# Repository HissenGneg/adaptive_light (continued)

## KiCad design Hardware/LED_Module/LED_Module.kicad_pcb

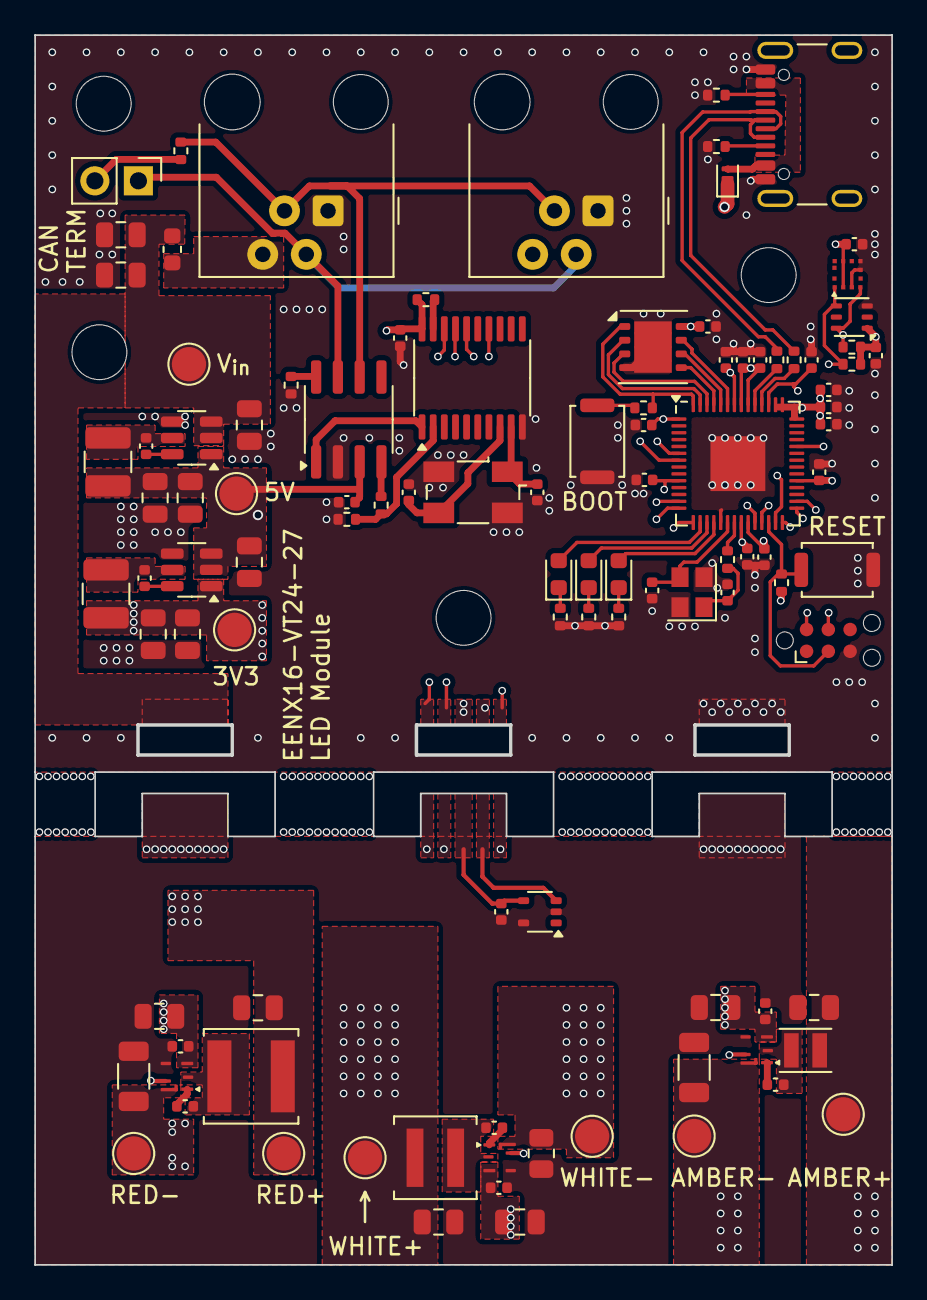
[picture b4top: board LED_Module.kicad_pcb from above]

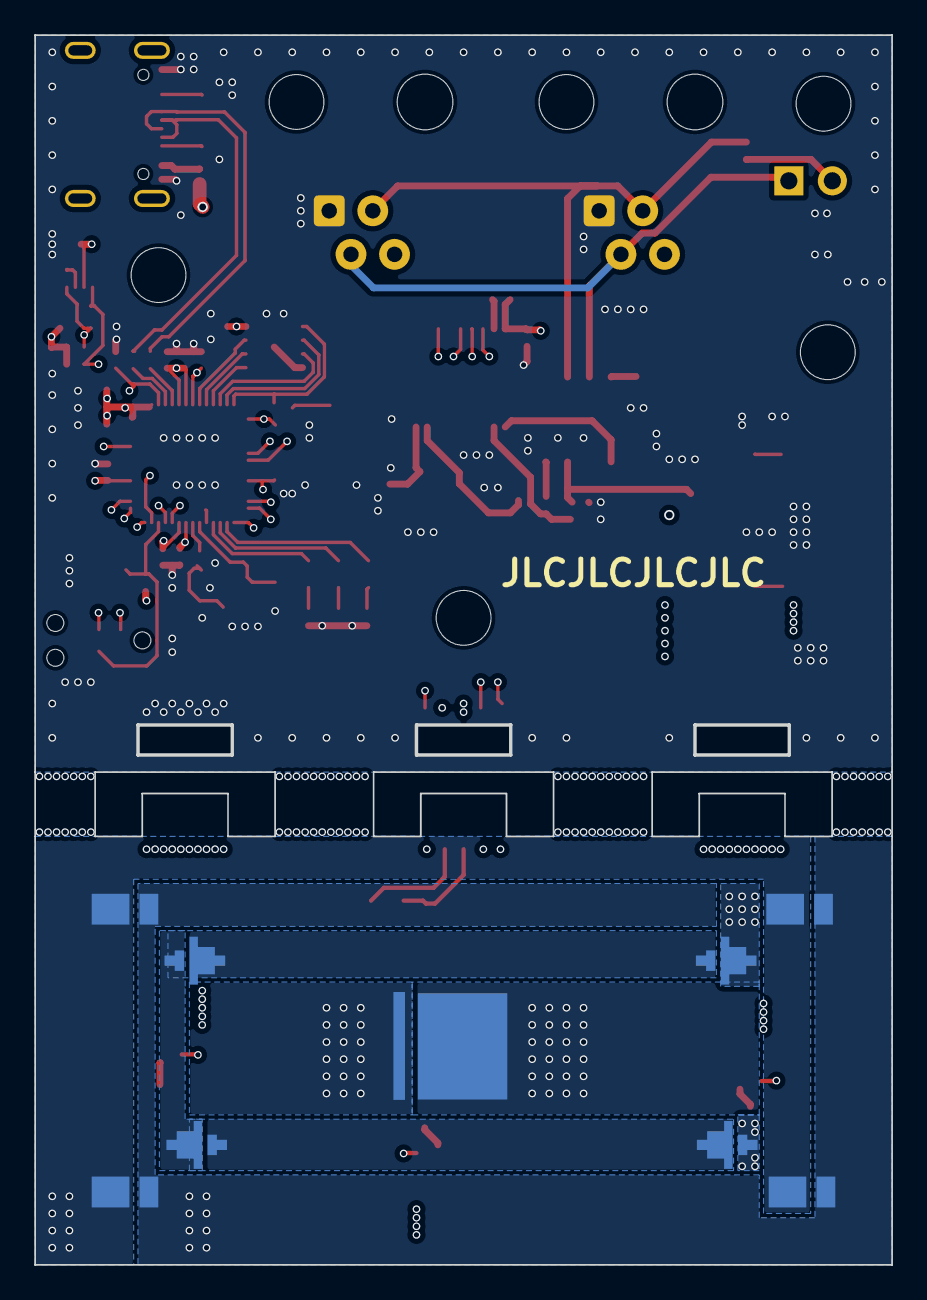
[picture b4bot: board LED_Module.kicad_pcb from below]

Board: 4 copper layers, 50.0 x 71.8 mm, 117 parts (9 on the bottom side), 71 nets.

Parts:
C201, C202, C302, C306, C501, C503, C507, C508, C509, C512: 10u; C_0805_2012Metric
C203, C204, C301, C305, C401, C402, C403, C404, C405, C406, C407, C408, C409, C411, C412, C413, C502, C504, C505, C506, C510, C511, C513, C601, C602: 100n; C_0402_1005Metric
C205, C206, C414, C415: 10p; C_0402_1005Metric
C303, C304, C307, C308: 22u; C_0805_2012Metric
C410: 1u; C_0402_1005Metric
D401: D_Schottky; Nexperia_DSN1608-2_1.6x0.8mm
D501, D503, D504, D505: LED-red; KR DMLQ32. 23
D502: LED-main; LUXEON 7070
D506, D507, D508, D509: LED-amber; JE2835_Amber
D601: R; LED_0603_1608Metric
D602: G; LED_0603_1608Metric
D603: B; LED_0603_1608Metric
F201: 4A; Fuse_0603_1608Metric
H101, H102, H103, H104: MountingHole; MountingHole_3.2mm_M3
J201, J202: RJ9; RJ9_Evercom_5301-440xxx_Horizontal
J401: USB_C_Receptacle_USB2.0_16P; USB_C_Receptacle_GCT_USB4105-xx-A_16P_TopMnt_Horizontal
J402: TagConnect_SWD; Tag-Connect_TC2030-IDC-NL_2x03_P1.27mm_Vertical
JP201: Jumper_termination; PinHeader_1x02_P2.54mm_Vertical
L301, L302: 4u7; L_1210_3225Metric
L501: 20u; L_Changjiang_FNR5045S
L502: 15u; L_Coilcraft_XAL4040-XXX
L503: 5.6u; L_Sunlord_SWPA252012S
R201, R603, R604, R605: 120; R_0402_1005Metric
R202, R401, R402, R601, R602: 5k1; R_0402_1005Metric
R203, R204, R205, R403: 10k; R_0402_1005Metric
R404, R407: 1k; R_0402_1005Metric
R405, R406: 27; R_0402_1005Metric
R501: 100m; R_0805_2012Metric
R502, R503: 200m; R_1206_3216Metric
SW401, SW402: SW_Push; SW_Push_SPST_NO_Alps_SKRK
TP201: TPVin; TestPoint_Pad_D2.0mm
TP301: TP3V3; TestPoint_Pad_D2.0mm
TP302: TP5V; TestPoint_Pad_D2.0mm
TP501: TPLED2+; TestPoint_Pad_D2.0mm
TP502: TPLED1+; TestPoint_Pad_D2.0mm
TP503: TPLED1-; TestPoint_Pad_D2.0mm
TP504: TPLED2-; TestPoint_Pad_D2.0mm
TP505: TPLED3+; TestPoint_Pad_D2.0mm
TP506: TPLED3-; TestPoint_Pad_D2.0mm
U201: MCP2551-I-SN; SOIC-8_3.9x4.9mm_P1.27mm
U202: MCP2515-xST; TSSOP-20_4.4x6.5mm_P0.65mm
U301: AP63203WU; TSOT-23-6
U302: AP63205WU; TSOT-23-6
U401: W25Q64JVXGIQ; WSON-8-1EP_4x4mm_P0.8mm_EP2.2x3mm
U402: RP2040; QFN-56-1EP_7x7mm_P0.4mm_EP3.2x3.2mm
U501, U502, U503: TPS92200; VQFN-HR-6pin-TexasInstruments
U504: TMP236; SOT-353_SC-70-5
U601: MC3479
U602: LTR-303ALS-01; Lite-On_LTR-303ALS-01
Y201: 8M; Crystal_SMD_Abracon_ABM3B-4Pin_5.0x3.2mm
Y401: 12M; Crystal_SMD_2520-4Pin_2.5x2.0mm

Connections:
+1V1: C410.1, C411.1, C412.1, U402.23 (DVDD), U402.45 (VREG_VOUT), U402.50 (DVDD)
+3V3: C203.1, C303.1, C304.1, C401.1, C402.1, C403.1, C404.1, C405.1, C406.1, C407.1, C408.1, C409.1, C413.1, C513.1, C601.1, C602.1, L301.2, R205.1, R403.1, R601.1, R602.1, TP301.1, U202.20 (VDD), U301.1 (FB), U401.8 (VCC), U402.1 (IOVDD), U402.10 (IOVDD), U402.22 (IOVDD), U402.33 (IOVDD), U402.42 (IOVDD), U402.43 (ADC_AVDD), U402.44 (VREG_IN), U402.48 (USB_VDD), U402.49 (IOVDD), U504.4 (V_{DD}), U601.2 (CSN), U601.9 (VDD), U602.1 (VDD)
+5V: C204.1, C302.1, C307.1, C308.1, D401.1 (K), L302.2, TP302.1, U201.3 (VDD), U301.2 (EN), U301.3 (IN), U302.1 (FB)
+SYSTEM: C201.1, C202.1, C306.1, C501.1, C502.1, C503.1, C504.1, C509.1, C510.1, F201.2, TP201.1, U302.2 (EN), U302.3 (IN), U501.3 (Vin), U502.3 (Vin), U503.3 (Vin)
/CAN_bus/CANH: J201.2, J202.2, JP201.1 (A), U201.7 (CANH)
/CAN_bus/CANL: J201.3, J202.3, R201.2, U201.6 (CANL)
/LED_TEMP: U402.38 (GPIO26_ADC0), U504.3 (V_{OUT})
/MISO: U202.17 (SO), U402.27 (GPIO16)
/MOSI: U202.16 (SI), U402.30 (GPIO19)
/Microcontroller/FLASH_CLK: U401.6 (CLK), U402.52 (QSPI_SCLK)
/Microcontroller/FLASH_IO0: U401.5 (DI(IO0)), U402.53 (QSPI_SD0)
/Microcontroller/FLASH_IO1: U401.2 (DO(IO1)), U402.55 (QSPI_SD1)
/Microcontroller/FLASH_IO2: U401.3 (IO2), U402.54 (QSPI_SD2)
/Microcontroller/FLASH_IO3: U401.7 (IO3), U402.51 (QSPI_SD3)
/Microcontroller/FLASH_~CS: R404.2, U401.1 (~CS), U402.56 (QSPI_SS)
/Microcontroller/RP2040_D+: R405.2, U402.47 (USB_DP)
/Microcontroller/RP2040_D-: R406.2, U402.46 (USB_DM)
/Microcontroller/SWCLK: J402.4 (SWCLK), U402.24 (SWCLK)
/Microcontroller/SWD: J402.2 (SWDIO), U402.25 (SWD)
/Microcontroller/USB_D+: J401.A6 (D+), J401.B6 (D+), R405.1
/Microcontroller/USB_D-: J401.A7 (D-), J401.B7 (D-), R406.1
/Microcontroller/XIN: C414.2, U402.20 (XIN), Y401.3
/Microcontroller/XOUT: R407.2, U402.21 (XOUT)
/Microcontroller/XOUT_R: C415.2, R407.1, Y401.1
/Microcontroller/~RESET: J402.3 (~RESET), R403.2, SW401.1, U402.26 (RUN)
/PWM_AMBER: U402.15 (GPIO12), U503.5 (DIM)
/PWM_RED: U402.14 (GPIO11), U501.5 (DIM)
/PWM_WHITE: U402.13 (GPIO10), U502.5 (DIM)
/SCK: U202.14 (SCK), U402.29 (GPIO18)
/SCL: R601.2, U402.7 (GPIO5), U601.1 (SCK_SCL), U602.4 (SCL)
/SDA: R602.2, U402.6 (GPIO4), U601.4 (DIN_SDA), U602.6 (SDA)
/STATUS1: D603.2 (A), U402.18 (GPIO15)
/STATUS2: D601.2 (A), U402.17 (GPIO14)
/STATUS3: D602.2 (A), U402.16 (GPIO13)
/~CS: U202.18 (~CS), U402.28 (GPIO17)
GND: C201.2, C202.2, C203.2, C204.2, C205.1, C206.1, C302.2, C303.2, C304.2, C306.2, C307.2, C308.2, C401.2, C402.2, C403.2, C404.2, C405.2, C406.2, C407.2, C408.2, C409.2, C410.2, C411.2, C412.2, C413.2, C414.1, C415.1, C501.2, C502.2, C503.2, C504.2, C507.2, C508.2, C509.2, C510.2, C512.2, C513.2, C601.2, C602.2, J201.1, J202.1, J401.A1 (GND), J401.A12 (GND), J401.B1 (GND), J401.B12 (GND), J402.5 (GND), R203.2, R204.2, R401.2, R402.2, R501.2, R502.2, R503.2, R603.2, R604.2, R605.2, SW401.2, SW402.1, U201.2 (VSS), U202.10 (VSS), U301.4 (GND), U302.4 (GND), U401.4 (GND), U401.9 (EP), U402.19 (TESTEN), U402.57 (GND), U501.4 (GND), U502.4 (GND), U503.4 (GND), U504.2 (GND), U504.5 (GND), U601.3 (DOUT_A6), U601.6 (GND), U601.7 (VPP), U602.3 (GND), Y201.2, Y201.4, Y401.2, Y401.4
unnamed: D401.2 (A), J401.A4 (VBUS), J401.A9 (VBUS), J401.B4 (VBUS), J401.B9 (VBUS)
unnamed: C507.1, D501.2 (A), L501.2, TP501.1
unnamed: D501.1 (K), D503.2 (A)
unnamed: C508.1, D502.2 (A), L502.2, TP502.1
unnamed: D502.1 (K), R501.1, TP503.1, U502.6 (FB)
unnamed: D503.1 (K), D504.2 (A)
unnamed: D504.1 (K), D505.2 (A)
unnamed: D505.1 (K), R502.1, TP504.1, U501.6 (FB)
unnamed: C512.1, D506.2 (A), D507.2 (A), D508.2 (A), D509.2 (A), L503.2, TP505.1
unnamed: D506.1 (K), D507.1 (K), D508.1 (K), D509.1 (K), R503.1, TP506.1, U503.6 (FB)
unnamed: D601.1 (K), R603.1
unnamed: D602.1 (K), R604.1
unnamed: D603.1 (K), R605.1
unnamed: F201.1, J201.4, J202.4
unnamed: J401.A5 (CC1), R402.1
unnamed: J401.B5 (CC2), R401.1
unnamed: JP201.2 (B), R201.1
unnamed: R404.1, SW402.2
unnamed: R202.1, U201.4 (RXD)
unnamed: R204.1, U201.8 (Rs)
unnamed: U201.1 (TXD), U202.1 (TXCAN)
unnamed: C206.2, U202.9 (OSC1), Y201.1
unnamed: C205.2, U202.8 (OSC2), Y201.3
unnamed: R202.2, R203.1, U202.2 (RXCAN)
unnamed: R205.2, U202.19 (~RESET)
unnamed: C301.2, U301.6 (BST)
unnamed: C301.1, L301.1, U301.5 (SW)
unnamed: C305.2, U302.6 (BST)
unnamed: C305.1, L302.1, U302.5 (SW)
unnamed: C505.1, U501.1 (BOOT)
unnamed: C505.2, L501.1, U501.2 (SW)
unnamed: C506.1, U502.1 (BOOT)
unnamed: C506.2, L502.1, U502.2 (SW)
unnamed: C511.1, U503.1 (BOOT)
unnamed: C511.2, L503.1, U503.2 (SW)

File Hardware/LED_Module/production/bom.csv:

Designator,Footprint,Quantity,Value,LCSC Part #
"C201, C202, C302, C306, C501, C503, C507, C508, C509, C512",0805,10,10u,
"C203, C204, C301, C305, C401, C402, C403, C404, C405, C406, C407, C408, C409, C411, C412, C413, C502, C504, C505, C506, C510, C511, C513, C601, C602",0402,25,100n,
"C205, C206, C414, C415",0402,4,10p,
"C303, C304, C307, C308",0805,4,22u,
C410,0402,1,1u,
D401,Nexperia_DSN1608-2_1.6x0.8mm,1,D_Schottky,
D501,KR DMLQ32. 23,1,LED-red,KR DMLQ32.23-6K6M-26-M3W3
D502,LUXEON 7070,1,LED-main, L170-3070701200000 
"D503, D504, D505",KR DMLQ32. 23,3,LED-red,https://www.mouser.se/ProductDetail/ams-OSRAM/KR-DMLQ32.23-6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
"D506, D507, D508, D509",JE2835_Amber,4,LED-amber, JE2835AAM-N-0001A0000-N0000001
D601,0603,1,R,
D602,0603,1,G,
D603,0603,1,B,
F201,0603,1,4A,
"H101, H102, H103, H104",MountingHole_3.2mm_M3,4,MountingHole,
"J201, J202",RJ9_Evercom_5301-440xxx_Horizontal,2,RJ9,
J401,USB_C_Receptacle_GCT_USB4105-xx-A_16P_TopMnt_Horizontal,1,USB_C_Receptacle_USB2.0_16P,
JP201,PinHeader_1x02_P2.54mm_Vertical,1,Jumper_termination,
"L301, L302",1210,2,4u7,
L501,L_Changjiang_FNR5045S,1,20u,
L502,L_Coilcraft_XAL4040-XXX,1,15u,
L503,L_Sunlord_SWPA252012S,1,5.6u,
"R201, R603, R604, R605",0402,4,120,
"R202, R401, R402, R601, R602",0402,5,5k1,
"R203, R204, R205, R403",0402,4,10k,
"R404, R407",0402,2,1k,
"R405, R406",0402,2,27,
R501,0805,1,100m,
"R502, R503",1206,2,200m,
"SW401, SW402",SW_Push_SPST_NO_Alps_SKRK,2,SW_Push,
TP201,TestPoint_Pad_D2.0mm,1,TPVin,
TP301,TestPoint_Pad_D2.0mm,1,TP3V3,
TP302,TestPoint_Pad_D2.0mm,1,TP5V,
TP501,TestPoint_Pad_D2.0mm,1,TPLED2+,
TP502,TestPoint_Pad_D2.0mm,1,TPLED1+,
TP503,TestPoint_Pad_D2.0mm,1,TPLED1-,
TP504,TestPoint_Pad_D2.0mm,1,TPLED2-,
TP505,TestPoint_Pad_D2.0mm,1,TPLED3+,
TP506,TestPoint_Pad_D2.0mm,1,TPLED3-,
U201,SOIC-8_3.9x4.9mm_P1.27mm,1,MCP2551-I-SN,
U202,TSSOP-20_4.4x6.5mm_P0.65mm,1,MCP2515-xST,
U301,TSOT-23-6,1,AP63203WU,
U302,TSOT-23-6,1,AP63205WU,
U401,WSON-8-1EP_4x4mm_P0.8mm_EP2.2x3mm,1,W25Q64JVXGIQ,
U402,QFN-56-1EP_7x7mm_P0.4mm_EP3.2x3.2mm,1,RP2040,
"U501, U502, U503",VQFN-HR-6pin-TexasInstruments,3,TPS92200,
U504,SOT-353_SC-70-5,1,TMP236,
U601,MC3479,1,MC3479,
U602,Lite-On_LTR-303ALS-01,1,LTR-303ALS-01,
Y201,Crystal_SMD_Abracon_ABM3B-4Pin_5.0x3.2mm,1,8M,
Y401,Crystal_SMD_2520-4Pin_2.5x2.0mm,1,12M,

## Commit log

2024-02-29 La till allt
    yes
2024-03-01 Controller fixades
2024-03-19 La in allt
    Myyycket saker
2024-03-19 User interface fix
2024-03-20 LED module go brrrrrrrrrrrrrrrrrr
2024-03-24 User interface and Controller done
    yes
2024-03-26 Changes and fixes
2024-03-26 final fixes (hopefully) (GONE WRONG?!) (real)
2024-05-02 Add software files
